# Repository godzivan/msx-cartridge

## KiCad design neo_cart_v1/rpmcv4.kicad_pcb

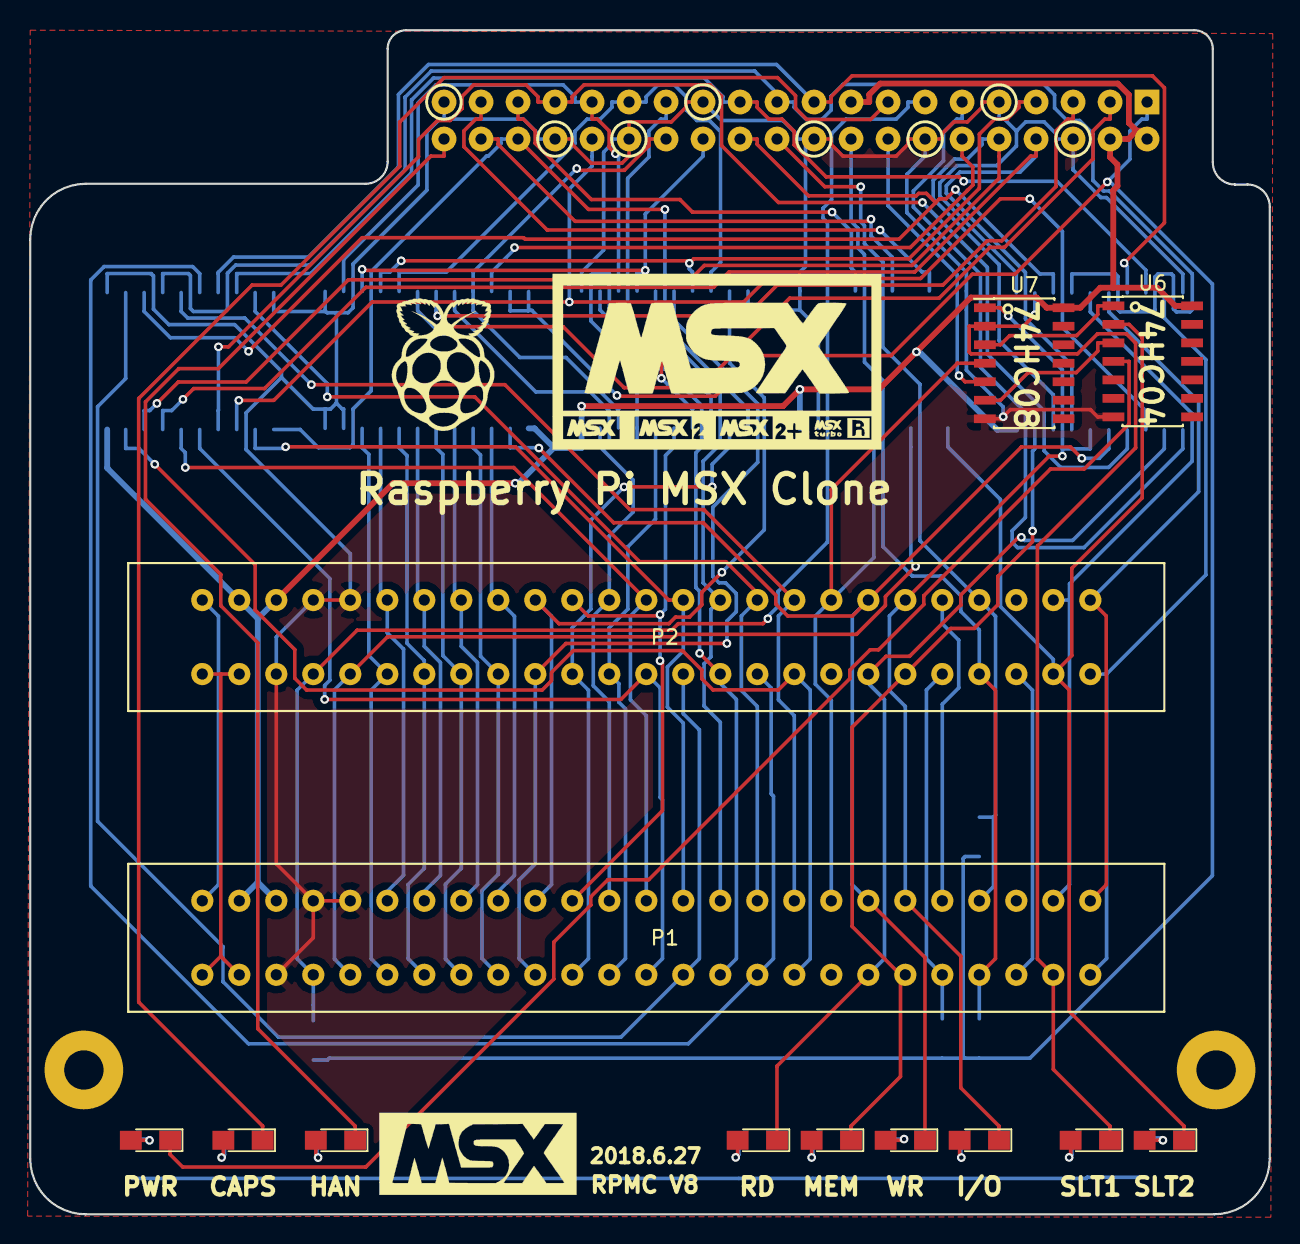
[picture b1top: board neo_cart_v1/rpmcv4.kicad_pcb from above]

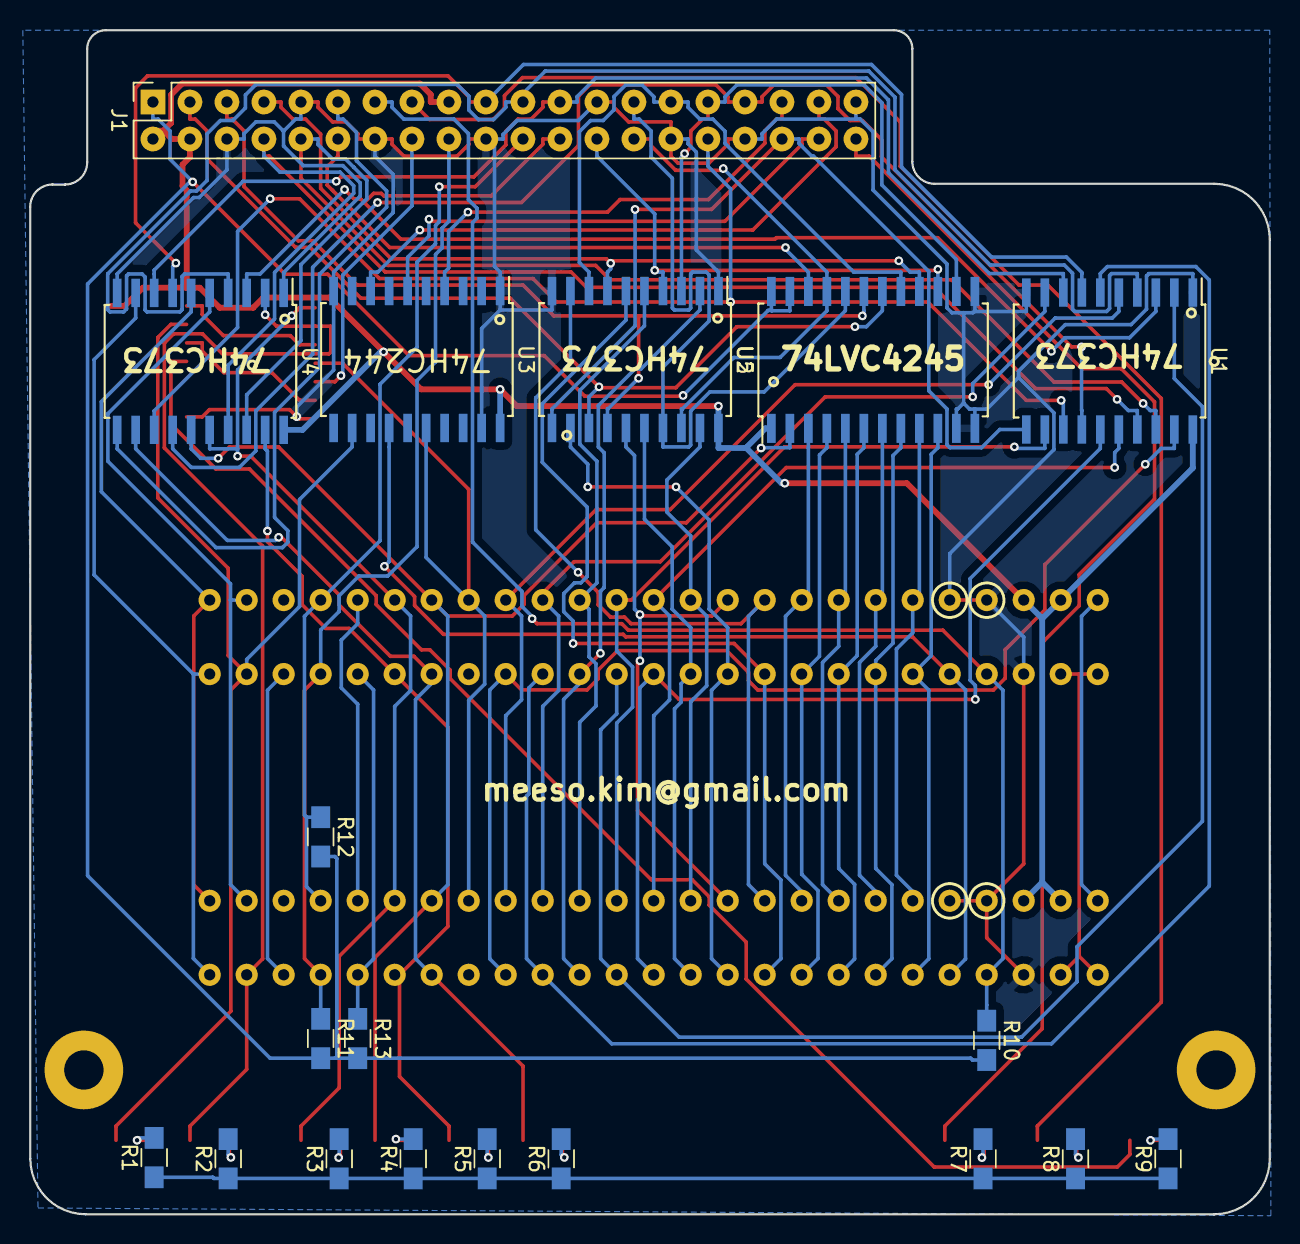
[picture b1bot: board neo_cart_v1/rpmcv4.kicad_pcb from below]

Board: 2 copper layers, 85.1 x 81.3 mm, 36 parts (19 on the bottom side), 84 nets.

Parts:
D1, D2, D3, D4, D5, D6, D7, D8, D9: Led_Small; LED_0805_HandSoldering
G1: LOGO; raspberry_pi_logo
G2: LOGO; msx_msx2_msx+logo
J1: RPi_GPIO; Socket_Strip_Straight_2x20_Pitch2.54mm
P1, P2: CONN_02X25; MSX_SLOT
R1, R2, R3, R4, R5, R6, R7, R8, R9, R10, R11, R12, R13: R; R_0805_HandSoldering
REF3, REF4: MountingHole_2.7mm_Pad
U1, U2, U4: 74LS373; SOIC-20W_7.5x12.8mm_Pitch1.27mm
U3: 74HC244; SOIC-20W_7.5x12.8mm_Pitch1.27mm
U5: LVC4245; SOIC-24W_7.5x15.4mm_Pitch1.27mm
U6: 74HC04; SOIC-14_3.9x8.7mm_Pitch1.27mm
U7: 74LS08; SOIC-14_3.9x8.7mm_Pitch1.27mm

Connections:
+3V3: J1.1, R10.2, R11.2, R12.2, R13.2, U5.23, U5.24
+5V: J1.2, J1.4, J1.17, P1.45, P1.47, P2.45, P2.47, U1.20, U2.20, U3.20, U4.20, U5.1, U6.14, U7.14
/+12V: P1.48, P1.50, P2.48, P2.50
/A0: P1.28, P2.28, U2.16
/A1: P1.27, P2.27, U2.19
/A2: P1.30, P2.30, U2.12
/A3: P1.29, P2.29, U2.15
/A4: P1.32, P2.32, U2.6
/A5: P1.31, P2.31, U2.9
/A6: P1.22, P2.22, U2.2
/A7: P1.21, P2.21, U2.5
/A8: P1.24, P2.24, U1.2
/A9: P1.17, P2.17, U1.5
/A10: P1.20, P2.20, U1.6
/A11: P1.19, P2.19, U1.9
/A12: P1.23, P2.23, U1.12
/A13: P1.26, P2.26, U1.15
/A14: P1.25, P2.25, U1.16
/A15: P1.18, P2.18, U1.19
/BUSDIR: P1.10, P2.10, R13.1
/CAPS: D8.1, J1.15
/CLK: P1.42, P2.42, U3.14
/CS1: P1.1, P2.1, U4.6
/CS2: P1.2, P2.2, U4.9
/CS12: P1.3, P2.3, U4.5
/D0: P1.34, P2.34, U5.4
/D1: P1.33, P2.33, U5.3
/D2: P1.36, P2.36, U5.6
/D3: P1.35, P2.35, U5.5
/D4: P1.38, P2.38, U5.8
/D5: P1.37, P2.37, U5.7
/D6: P1.40, P2.40, U5.10
/D7: P1.39, P2.39, U5.9
/HAN: D7.1, J1.40
/INT: J1.18, P1.8, P2.8, R11.1
/IORQ: D3.1, P1.11, P2.11, U4.16, U7.1
/M1: P1.9, P2.9
/MREQ: D5.1, P1.12, P2.12, U4.19
/PWR: D9.1, U6.4
/RA8: J1.24, U1.3, U4.3
/RA9: J1.21, U1.4, U4.4
/RA10: J1.19, U1.7, U4.7
/RA11: J1.23, U1.8, U4.8
/RA12: J1.32, U1.13, U4.13
/RA13: J1.33, U1.14, U4.14
/RA14: J1.8, U1.17, U4.17
/RA15: J1.10, U1.18, U4.18
/RC16: J1.36, U1.11, U2.11
/RC17: J1.11, U4.11
/RC18: J1.12, U5.22
/RC19: J1.35, U3.4
/RC20: J1.38, U3.6
/RC23: J1.16, U7.5
/RC25: J1.22, P1.7, P2.7, R12.1
/RC26: J1.37, U3.8
/RC27: J1.13, P1.44, P2.44, R10.1
/RD: D6.1, P1.14, P2.14, U4.12
/RD0: J1.27, U2.17, U5.20
/RD1: J1.28, U2.18, U5.21
/RD2: J1.3, U2.13, U5.18
/RD3: J1.5, U2.14, U5.19
/RD4: J1.7, U2.7, U5.16
/RD5: J1.29, U2.8, U5.17
/RD6: J1.31, U2.3, U5.14
/RD7: J1.26, U2.4, U5.15
/RESET: P1.15, P2.15, U3.16, U7.4
/RFSH: P1.6, P2.6
/SLTSL1: D2.1, P1.4, U4.2, U7.2
/SLTSL3: D1.1, P2.4, U3.12, U6.2
/SNDIN: P1.49, P2.49
/V3.3: R1.1, R2.1, R3.1, R4.1, R5.1, R6.1, R7.1, R8.1, R9.1
/WR: D4.1, P1.13, P2.13, U4.15, U5.2
/nPWR: U6.3, U7.6
/nSLTSL3: U6.1, U7.3
GND: J1.6, J1.9, J1.14, J1.20, J1.25, J1.30, J1.34, J1.39, P1.41, P1.43, P1.46, P2.41, P2.43, P2.46, U1.1, U1.10, U2.1, U2.10, U3.1, U3.10, U3.19, U4.1, U4.10, U5.11, U5.12, U5.13, U6.7, U7.7
unnamed: D1.2, R1.2
unnamed: D2.2, R2.2
unnamed: D3.2, R3.2
unnamed: D4.2, R4.2
unnamed: D5.2, R5.2
unnamed: D6.2, R6.2
unnamed: D7.2, R7.2
unnamed: D8.2, R8.2
unnamed: D9.2, R9.2

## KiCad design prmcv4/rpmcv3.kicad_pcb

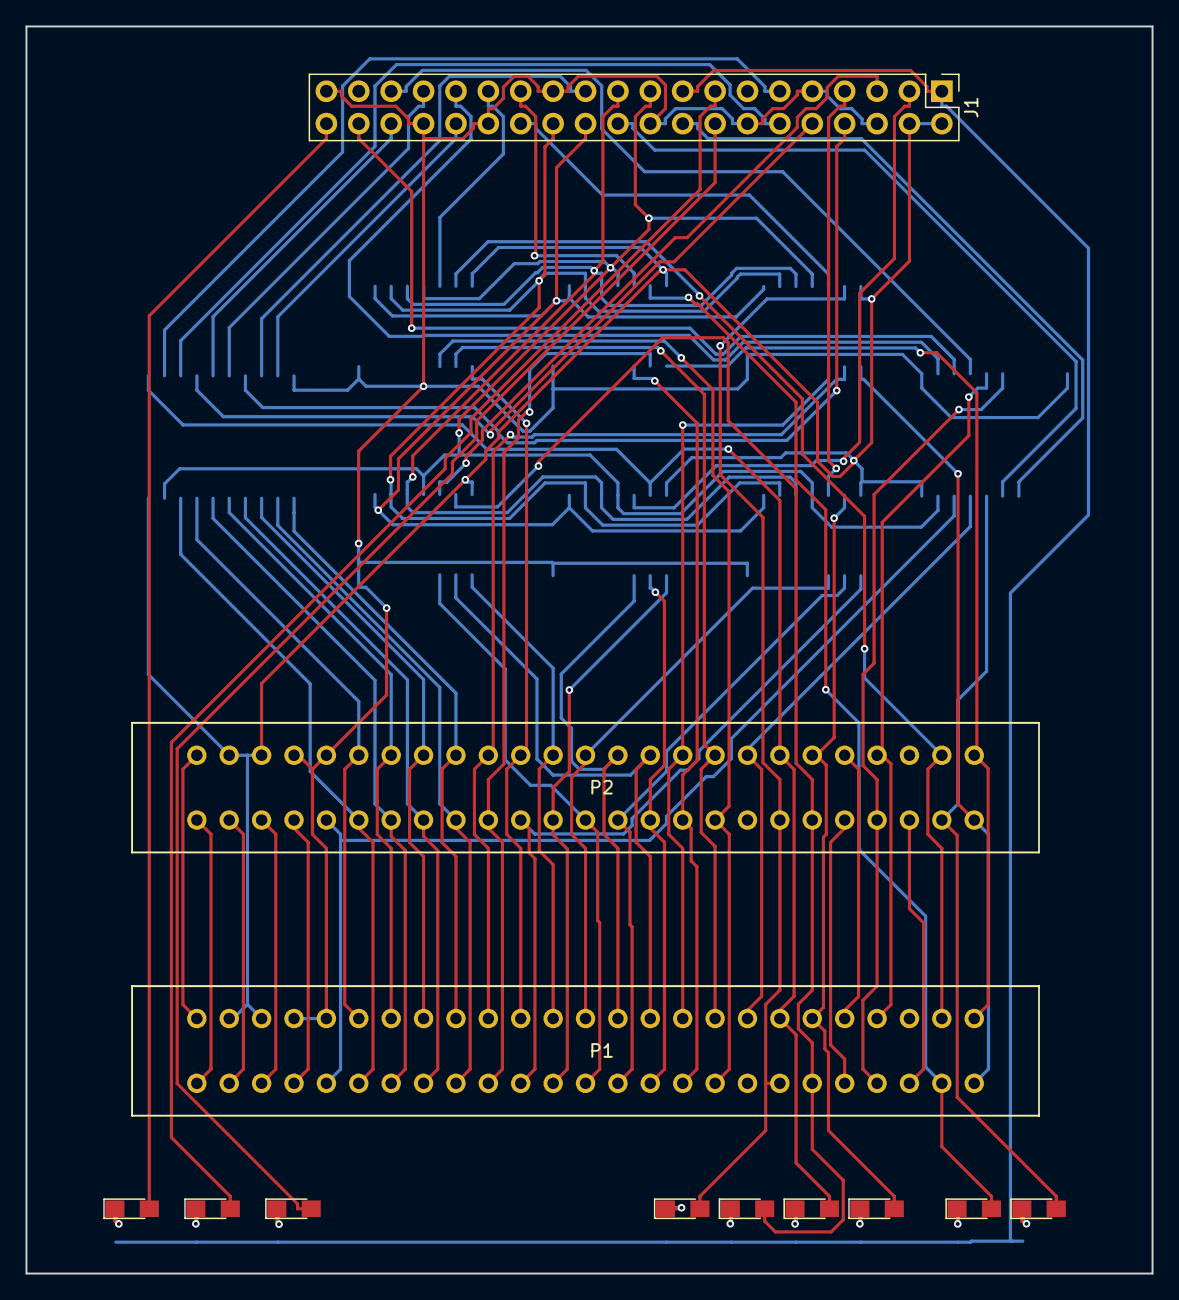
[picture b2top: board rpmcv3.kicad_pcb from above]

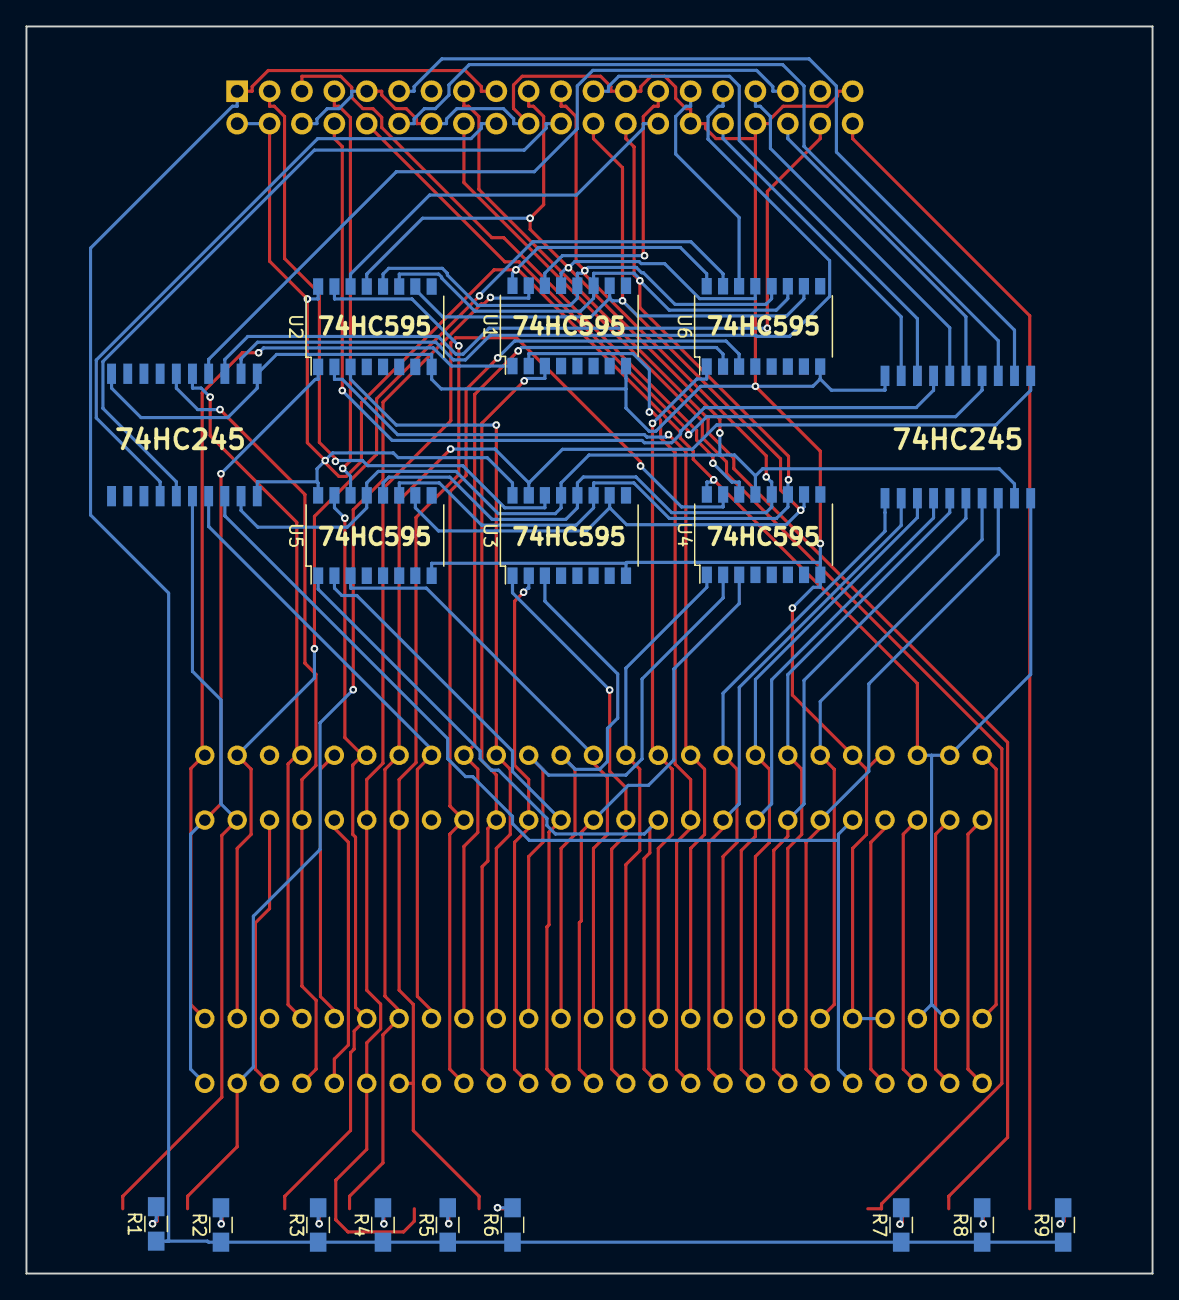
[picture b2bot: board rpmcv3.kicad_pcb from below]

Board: 2 copper layers, 88.3 x 97.8 mm, 29 parts (17 on the bottom side), 83 nets.

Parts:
D1, D2, D3, D4, D5, D6, D7, D8, D9: Led_Small; LED_0805_HandSoldering
J1: RPi_GPIO; Pin_Header_Straight_2x20_Pitch2.54mm
P1, P2: CONN_02X25; MSX_SLOT
R1, R2, R3, R4, R5, R6, R7, R8, R9: R; R_0805_HandSoldering
U1, U2, U3, U4, U5, U6: 74LS595; SOP-16_4.4x10.4mm_Pitch1.27mm
U7, U8: 74LS245; SOP20

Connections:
+3V3: J1.1, J1.17, R1.1, R2.1, R3.1, R4.1, R5.1, R6.1, R7.1, R8.1, R9.1
+5V: J1.2, J1.4, P1.45, P1.47, P2.45, P2.47, U1.16, U2.16, U3.16, U4.16, U5.16, U6.16, U7.20, U8.20
/+12V: P1.48, P2.48
/+V12: P1.50, P2.50
/A0: P1.28, P2.28, U3.1
/A1: P1.27, P2.27, U4.1
/A2: P1.30, P2.30, U5.1
/A3: P1.29, P2.29, U6.1
/A4: P1.32, P2.32, U1.2
/A5: P1.31, P2.31, U2.2
/A6: P1.22, P2.22, U3.2
/A7: P1.21, P2.21, U4.2
/A8: P1.24, P2.24, U5.2
/A9: P1.17, P2.17, U6.2
/A10: P1.20, P2.20, U1.3
/A11: P1.19, P2.19, U2.3
/A12: P1.23, P2.23, U3.3
/A13: P1.26, P2.26, U4.3
/A14: P1.25, P2.25, U5.3
/A15: P1.18, P2.18, U6.3
/BUSDIR: P1.10, P2.10
/CAPS: D8.2, J1.15
/CLK: P1.42, P2.42, U7.18
/CS1: P1.1, P2.1, U1.1
/CS2: P1.2, P2.2, U2.1
/CS12: P1.3, P2.3, U6.15
/D0: P1.34, P2.34, U8.12
/D1: P1.33, P2.33, U8.11
/D2: P1.36, P2.36, U8.14
/D3: P1.35, P2.35, U8.13
/D4: P1.38, P2.38, U8.16
/D5: P1.37, P2.37, U8.15
/D6: P1.40, P2.40, U8.18
/D7: P1.39, P2.39, U8.17
/HAN: D7.2, J1.16
/INT: P1.8, P2.8, U7.6
/IORQ: D3.2, P1.11, P2.11, U5.15
/LATCH: J1.21, U1.12, U2.12, U3.12, U4.12, U5.12, U6.12
/M1: P1.9, P2.9
/MOSI0: J1.27, U1.14
/MOSI1: J1.28, U2.14
/MOSI2: J1.3, U3.14
/MOSI3: J1.5, U4.14
/MOSI4: J1.7, U5.14
/MOSI5: J1.29, U6.14
/MREQ: D5.2, P1.12, P2.12, U4.15
/OE: J1.19, U1.13, U2.13, U3.13, U4.13, U5.13, U6.13, U7.19, U8.19
/PWR: D9.2, J1.40
/RCLK: J1.31, U7.2
/RD: D6.2, P1.14, P2.14, U2.15
/RD0: J1.23, U8.8
/RD1: J1.32, U8.9
/RD2: J1.33, U8.6
/RD3: J1.8, U8.7
/RD4: J1.10, U8.4
/RD5: J1.36, U8.5
/RD6: J1.11, U8.2
/RD7: J1.12, U8.3
/RESET: P1.15, P2.15, U7.17
/RFSH: P1.6, P2.6
/RINT: J1.18, U7.14
/RRESET: J1.38, U7.3
/RSLTSL3: J1.35, U7.4
/RWAIT: J1.22, U7.15
/SLTSL1: D2.2, P1.4, U1.15
/SLTSL3: D1.2, P2.4, U7.16
/SNDIN: P1.49, P2.49
/SRCLK: J1.26, U1.11, U2.11, U3.11, U4.11, U5.11, U6.11
/SRCLR: J1.24, U1.10, U2.10, U3.10, U4.10, U5.10, U6.10
/SW1: P1.44, P2.44
/SW2: P1.46, P2.46
/WAIT: P1.7, P2.7, U7.5
/WR: D4.2, P1.13, P2.13, U3.15, U8.1
GND: J1.6, J1.9, J1.14, J1.20, J1.25, J1.30, J1.34, J1.39, P1.41, P1.43, P2.41, P2.43, U1.8, U2.8, U3.8, U4.8, U5.8, U6.8, U7.1, U7.10, U8.10
unnamed: D1.1, R1.2
unnamed: D2.1, R2.2
unnamed: D3.1, R3.2
unnamed: D4.1, R4.2
unnamed: D5.1, R5.2
unnamed: D6.1, R6.2
unnamed: D7.1, R7.2
unnamed: D8.1, R8.2
unnamed: D9.1, R9.2

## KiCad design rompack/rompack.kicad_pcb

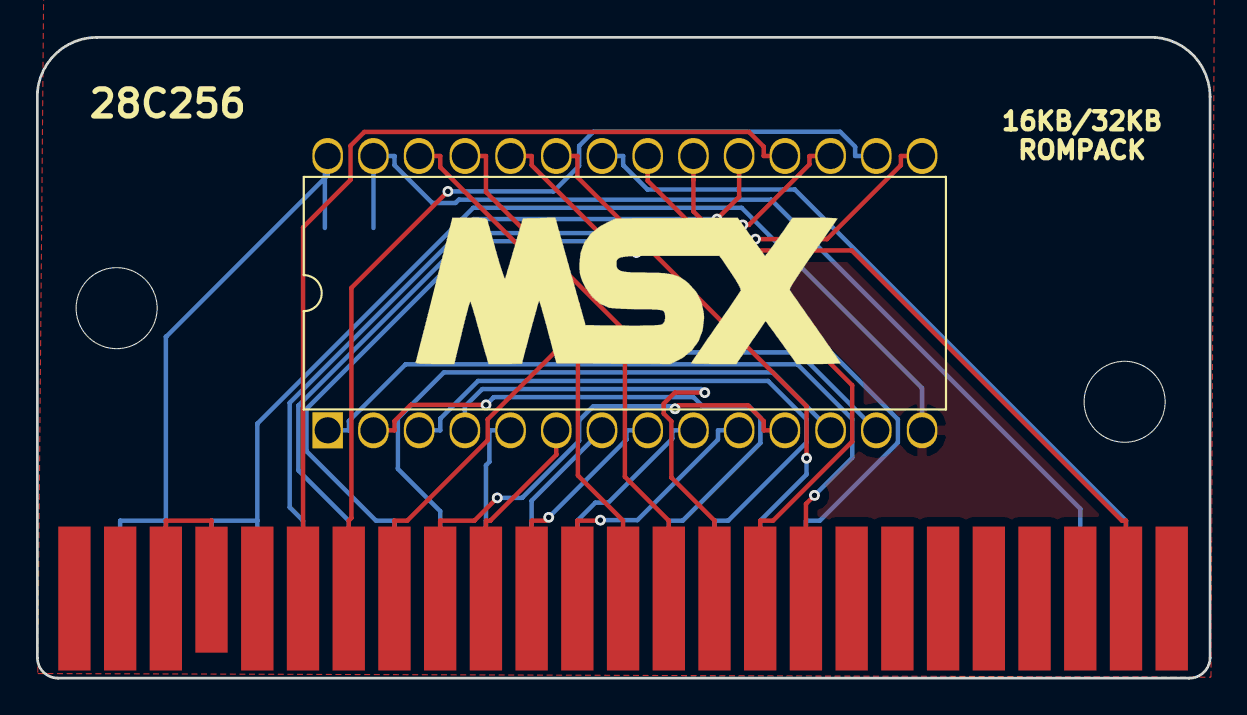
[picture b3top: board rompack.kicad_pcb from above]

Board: 2 copper layers, 65.2 x 35.6 mm, 4 parts (1 on the bottom side), 29 nets.

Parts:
G1: LOGO; msx-logo
P1: CONN_MSXSLOT; card_edge_connector
R1: R; R_0805_HandSoldering
U1: 28C256; DIP-28_W15.24mm

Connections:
/A0: P1.28, U1.10
/A1: P1.27, U1.9
/A2: P1.30, U1.8
/A3: P1.29, U1.7
/A4: P1.32, U1.6
/A5: P1.31, U1.5
/A6: P1.22, U1.4
/A7: P1.21, U1.3
/A8: P1.24, U1.25
/A9: P1.17, U1.24
/A10: P1.20, U1.21
/A11: P1.19, U1.23
/A12: P1.23, U1.2
/A13: P1.26, U1.26
/A14: P1.18, U1.1
/CS12: P1.3, U1.22
/D0: P1.34, U1.11
/D1: P1.33, U1.12
/D2: P1.36, U1.13
/D3: P1.35, U1.15
/D4: P1.38, U1.16
/D5: P1.37, U1.17
/D6: P1.40, U1.18
/D7: P1.39, U1.19
/SLTSL: P1.4, U1.20
/WR0: P1.5, R1.1, U1.27
GND: P1.41, P1.43, U1.14
unnamed: P1.44, P1.46
VCC: P1.45, P1.47, R1.2, U1.28

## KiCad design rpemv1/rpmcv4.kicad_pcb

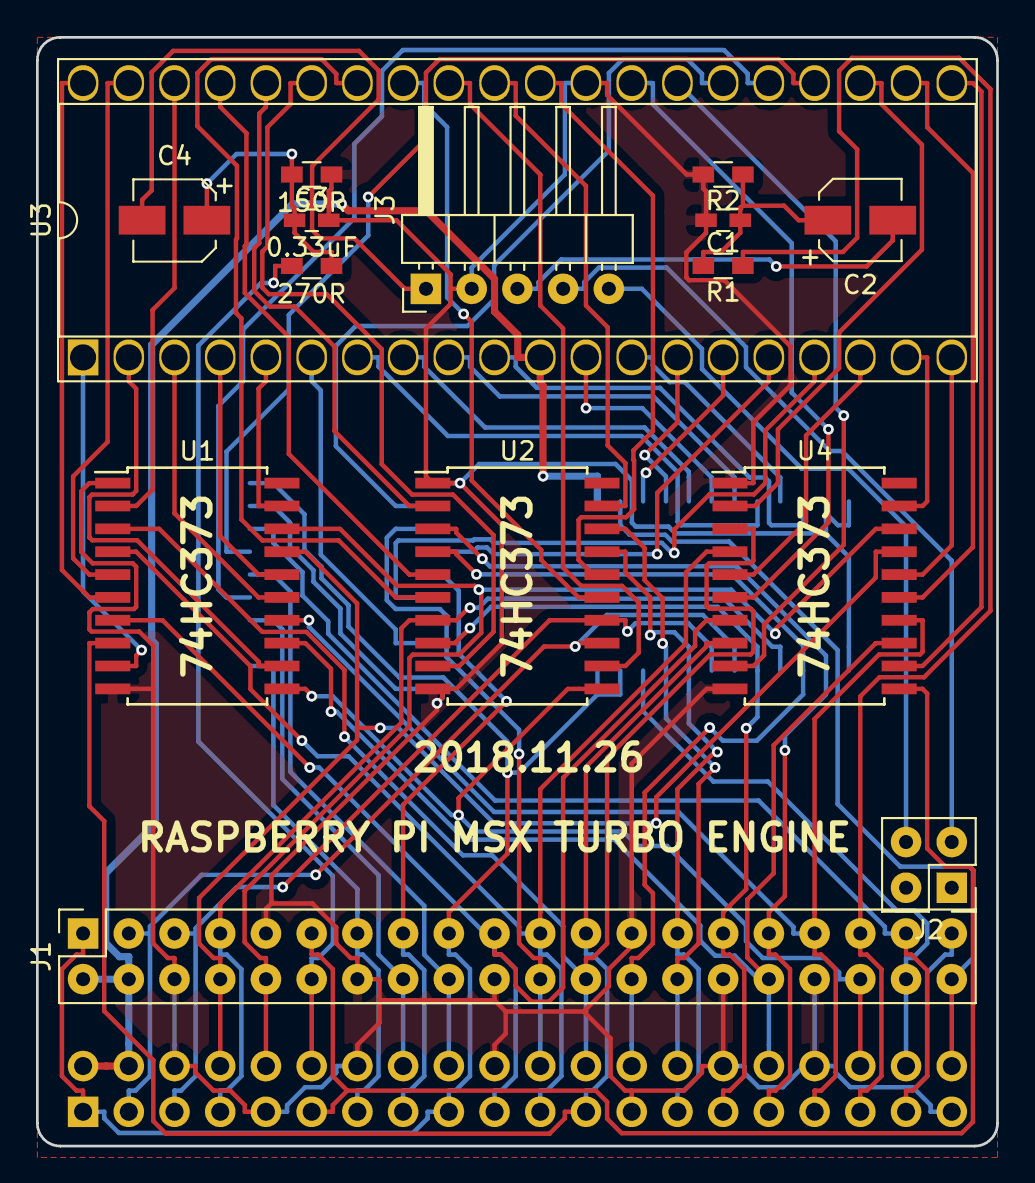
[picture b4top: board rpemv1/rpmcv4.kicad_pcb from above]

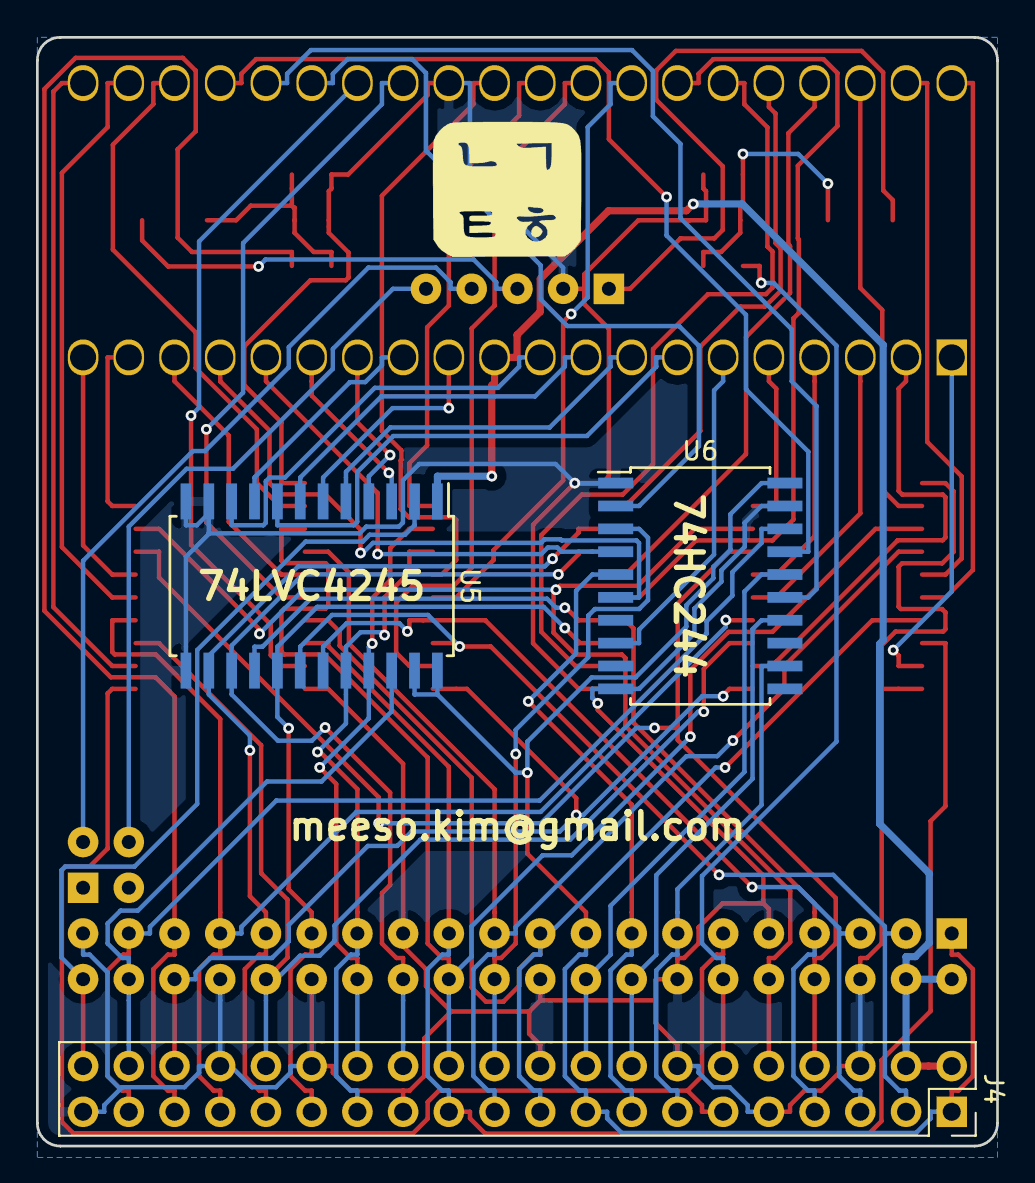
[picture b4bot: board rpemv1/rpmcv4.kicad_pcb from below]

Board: 2 copper layers, 53.3 x 61.6 mm, 18 parts (3 on the bottom side), 75 nets.

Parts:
C1, C3: 0.33uF; C_0603_HandSoldering
C2, C4: 10uF; CP_Elec_4x4.5
J1, J4: RPi_GPIO; Socket_Strip_Straight_2x20_Pitch2.54mm
J2: Conn_02x02_Odd_Even; Pin_Header_Straight_2x02_Pitch2.54mm
J3: Conn_01x05_Male; Pin_Header_Angled_1x05_Pitch2.54mm
R1, R3: 270R; R_0603_HandSoldering
R2, R4: 150R; R_0603_HandSoldering
U1, U2, U4: 74LS373; SOIC-20W_7.5x12.8mm_Pitch1.27mm
U3: Z80CPU; DIP-40_W15.24mm_Socket
U5: LVC4245; SOIC-24W_7.5x15.4mm_Pitch1.27mm
U6: 74HC244; SOIC-20W_7.5x12.8mm_Pitch1.27mm

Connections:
+3V3: J1.1, J1.17, J4.1, J4.17, U5.23, U5.24, U6.20
+5V: J1.2, J1.4, J4.2, J4.4, U3.11, U5.1
/A0: U2.16, U3.30
/A1: U2.19, U3.31
/A2: U2.12, U3.32
/A3: U2.15, U3.33
/A4: U2.6, U3.34
/A5: U2.9, U3.35
/A6: U2.2, U3.36
/A7: U2.5, U3.37
/A8: U1.2, U3.38
/A9: U1.5, U3.39
/A10: U1.6, U3.40
/A11: U1.9, U3.1
/A12: U1.12, U3.2
/A13: U1.15, U3.3
/A14: U1.16, U3.4
/A15: U1.19, U3.5
/BUSACK: U3.23, U4.2
/BUSRQ: U3.25, U6.15
/CLK: U3.6, U6.8
/D0: U3.14, U5.4
/D1: U3.15, U5.3
/D2: U3.12, U5.6
/D3: U3.8, U5.5
/D4: U3.7, U5.8
/D5: U3.9, U5.7
/D6: U3.10, U5.10
/D7: U3.13, U5.9
/HALT: U3.18, U4.5
/INT: U3.16, U6.4
/IORQ: U3.20, U4.16
/M1: U3.27, U4.9
/MREQ: U3.19, U4.19
/NMI: U3.17, U6.6
/RA8: J1.24, J4.24, U1.3, U4.3
/RA9: J1.21, J4.21, U1.4, U4.4
/RA10: J1.19, J4.19, U1.7, U4.7
/RA11: J1.23, J4.23, U1.8, U4.8
/RA12: J1.32, J4.32, U1.13, U4.13
/RA13: J1.33, J4.33, U1.14, U4.14
/RA14: J1.8, J4.8, U1.17, U4.17
/RA15: J1.10, J4.10, U1.18, U4.18
/RC16: J1.36, J4.36, U1.11, U2.11
/RC17: J1.11, J4.11, U4.11
/RC18: J1.12, J4.12, R3.1
/RC19: J1.35, J4.35, R1.1
/RC20: J1.38, J4.38, U5.22
/RC21: J1.40, J4.40, U5.2
/RC22: J1.15, J4.15, U6.5
/RC23: J1.16, J4.16, U6.14
/RC24: J1.18, J4.18, U6.16
/RC25: J1.22, J4.22, U6.3
/RC26: J1.37, J4.37, U6.18
/RC27: J1.13, J4.13, U6.12
/RD: U3.21, U4.12
/RD0: J1.27, J4.27, U2.17, U5.20
/RD1: J1.28, J4.28, U2.18, U5.21
/RD2: J1.3, J4.3, U2.13, U5.18
/RD3: J1.5, J4.5, U2.14, U5.19
/RD4: J1.7, J4.7, U2.7, U5.16
/RD5: J1.29, J4.29, U2.8, U5.17
/RD6: J1.31, J4.31, U2.3, U5.14
/RD7: J1.26, J4.26, U2.4, U5.15
/RESET: U3.26, U6.2
/RFSH: U3.28, U4.6
/WAIT: U3.24, U6.17
/WR: U3.22, U4.15
GND: C1.2, C3.2, J1.6, J1.9, J1.14, J1.20, J1.25, J1.30, J1.34, J1.39, J3.2, J4.6, J4.9, J4.14, J4.20, J4.25, J4.30, J4.34, J4.39, R2.2, R4.2, U1.1, U1.10, U2.1, U2.10, U3.29, U4.1, U4.10, U5.11, U5.12, U5.13, U6.1, U6.10, U6.19
unnamed: C1.1, C2.1, R1.2, R2.1
unnamed: C2.2, J3.3
unnamed: C3.1, C4.1, R3.2, R4.1
unnamed: C4.2, J3.1
unnamed: J2.3, J3.4
unnamed: J2.4, J3.5

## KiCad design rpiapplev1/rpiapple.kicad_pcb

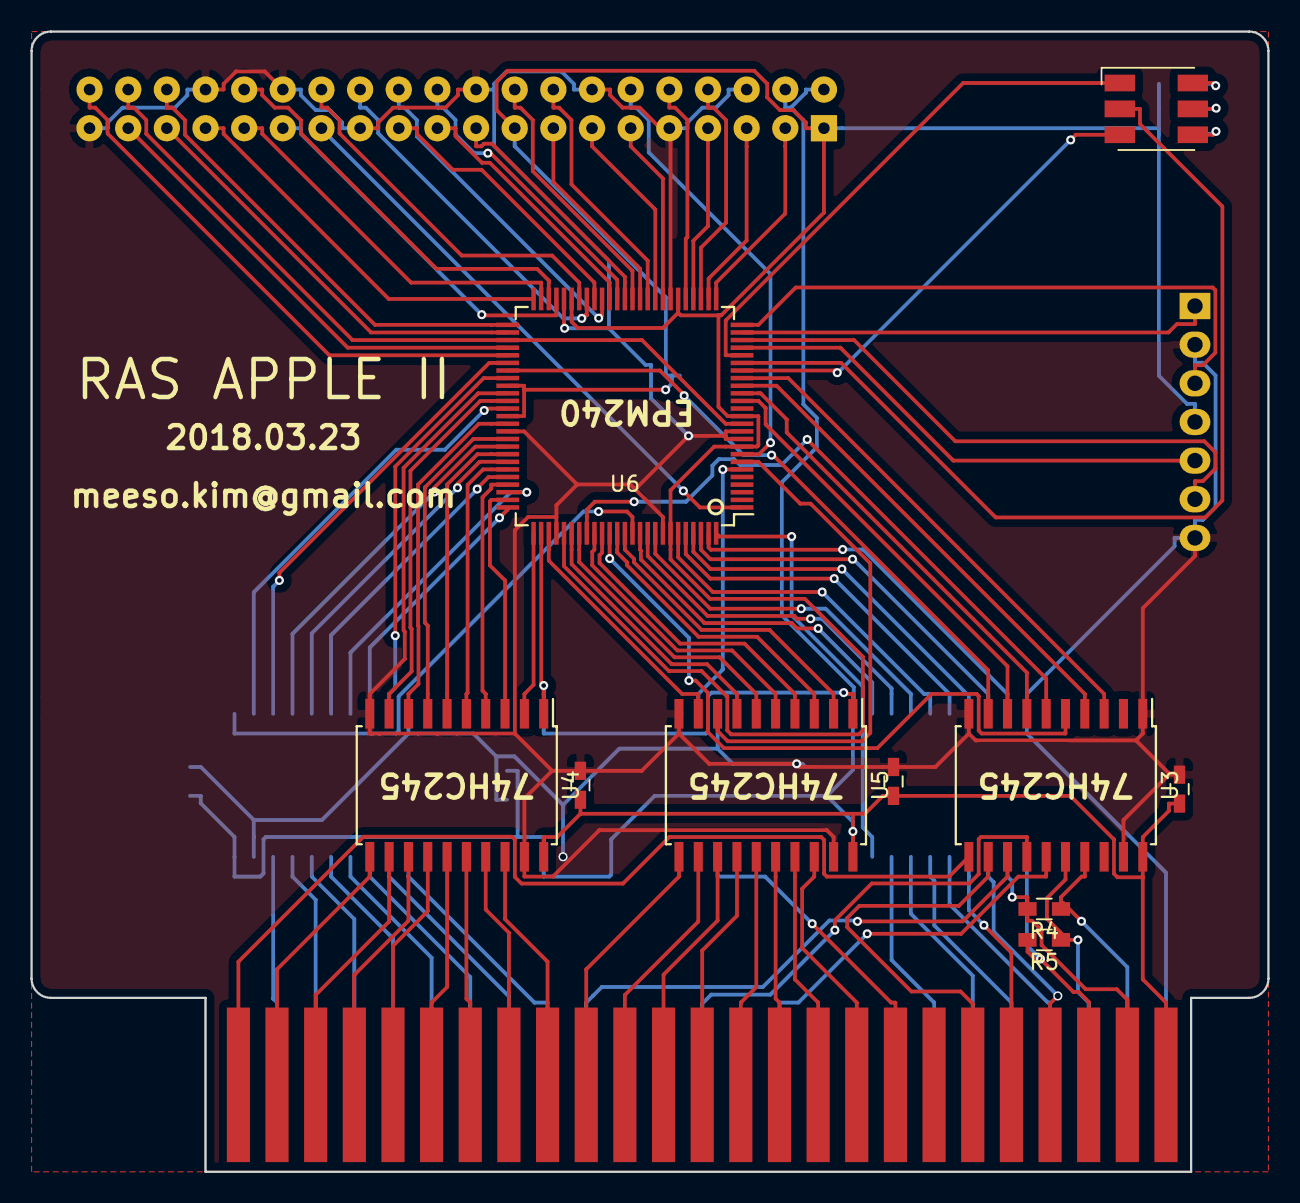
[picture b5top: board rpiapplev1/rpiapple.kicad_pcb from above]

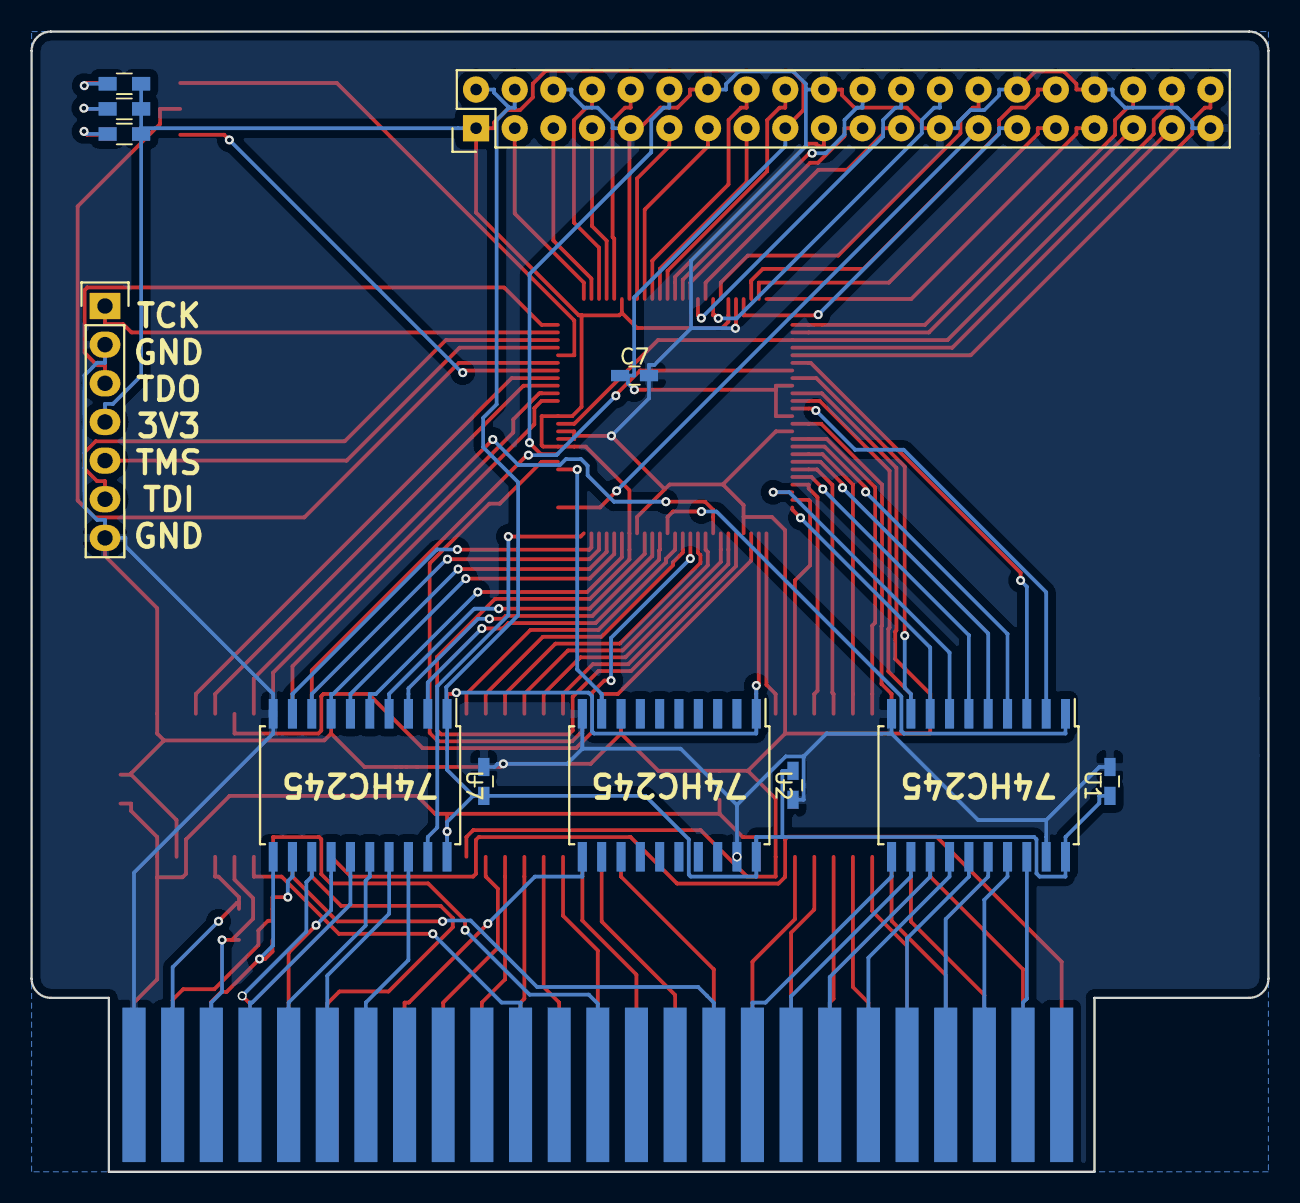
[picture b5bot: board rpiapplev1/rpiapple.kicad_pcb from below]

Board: 2 copper layers, 81.3 x 74.9 mm, 23 parts (12 on the bottom side), 124 nets.

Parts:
C1, C2, C3, C4, C5, C6, C7: C; C_0603_HandSoldering
D1: LED_RGB; LED_RGB_5050-6
J1: Raspberry_Pi_2_3; Pin_Header_Straight_2x20
J2: Conn_01x07; Pin_Header_Straight_1x07
P1: A2Bus; Male_Card-Edge_50_pin__100_mil
R1, R2, R3, R4, R5: R; R_0603_HandSoldering
U1, U2, U3, U4, U5, U7: 74HC245; SOIC-20W_7.5x12.8mm_Pitch1.27mm
U6: EMP240; TQFP-100_14x14mm_Pitch0.5mm

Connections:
/3V3: C7.1, J1.1, J1.17, J2.4, R1.1, R2.1, R3.1, U6.9, U6.13, U6.31, U6.45, U6.59, U6.63, U6.80, U6.94
/7M: P1.36, U3.15
/A0: P1.2, U4.11
/A1: P1.3, U4.12
/A2: P1.4, U4.13
/A3: P1.5, U4.14
/A4: P1.6, U4.15
/A5: P1.7, U4.16
/A6: P1.8, U4.17
/A7: P1.9, U4.18
/A8: P1.10, U5.11
/A9: P1.11, U5.12
/A10: P1.12, U5.13
/A11: P1.13, U5.14
/A12: P1.14, U5.15
/A13: P1.15, U5.16
/A14: P1.16, U5.17
/A15: P1.17, U5.18
/D0: P1.49, U1.18
/D1: P1.48, U1.17
/D2: P1.47, U1.16
/D3: P1.46, U1.15
/D4: P1.45, U1.14
/D5: P1.44, U1.13
/D6: P1.43, U1.12
/D7: P1.42, U1.11
/DEVSEL: P1.41, U3.13
/DMA: P1.22, U7.13
/DMAI: P1.27, R4.1, U3.17
/DMAO: P1.24, R4.2, U7.12
/INH: P1.32, U7.18
/INT0: P1.23, R5.2, U7.11
/INTI: P1.28, R5.1, U3.16
/IOSEL: P1.1, U3.11
/IOSTRB: P1.20, U3.12
/IRQ: P1.30, U7.16
/LED1: D1.3, U6.19
/LED2: D1.2, U6.20
/LED3: D1.1, U6.21
/NMI: P1.29, U7.15
/PH1: P1.38, U3.14
/RA0: J1.24, U6.41
/RA1: J1.21, U6.40
/RA2: J1.19, U6.38
/RA3: J1.23, U6.42
/RA4: J1.32, U6.48
/RA5: J1.33, U6.50
/RA6: J1.8, U6.28
/RA7: J1.10, U6.30
/RC0: J1.36, U6.51
/RC1: J1.11, U6.33
/RC2: J1.12, U6.8
/RC3: J1.35, U6.52
/RC4: J1.38, U6.12, U6.53
/RC5: J1.40, U6.55
/RC6: J1.15, U6.36
/RC7: J1.16, U6.35
/RC8: J1.18, U6.37
/RC9: J1.22, U6.39
/RC10: J1.37, U6.54
/RC11: J1.13, U6.34
/RD0: J1.27, U6.1
/RD1: J1.28, U6.44
/RD2: J1.3, U6.26
/RD3: J1.5, U6.27
/RD4: J1.7, U6.29
/RD5: J1.29, U6.47
/RD6: J1.31, U6.49
/RD7: J1.26, U6.43
/RDY: P1.21, U7.14
/RES: P1.31, U7.17
/RW: P1.18, U2.11
/T7M: U3.5, U6.86
/TA0: U4.9, U6.61
/TA1: U4.8, U6.64
/TA2: U4.7, U6.66
/TA3: U4.6, U6.68
/TA4: U4.5, U6.70
/TA5: U4.4, U6.72
/TA6: U4.3, U6.74
/TA7: U4.2, U6.76
/TA8: U5.9, U6.78
/TA9: U5.8, U6.7
/TA10: U5.7, U6.81
/TA11: U5.6, U6.82
/TA12: U5.5, U6.84
/TA13: U5.4, U6.85
/TA14: U5.3, U6.87
/TA15: U5.2, U6.88
/TCK: J2.1, U6.24
/TD0: U1.2, U6.62
/TD1: U1.3, U6.56
/TD2: U1.4, U6.67
/TD3: U1.5, U6.69
/TD4: U1.6, U6.71
/TD5: U1.7, U6.73
/TD6: U1.8, U6.75
/TD7: U1.9, U6.58
/TDEVSEL: U3.7, U6.16
/TDI: J2.6, U6.23
/TDIR: U2.1, U4.1, U5.1, U6.77
/TDIR2: U6.100, U7.19
/TDMA: U6.97, U7.7
/TDMAI: U3.3, U6.18
/TDMAO: U6.98, U7.8
/TDO: J2.3, U6.25
/TINH: U6.90, U7.2
/TINTI: U3.4, U6.17
/TINTO: U6.99, U7.9
/TIOSEL: U3.9, U6.57
/TIOSTRB: U3.8, U6.15
/TIRQ: U6.92, U7.4
/TMS: J2.5, U6.22
/TNMI: U6.95, U7.5
/TPH1: U3.6, U6.83
/TRDY: U6.96, U7.6
/TRES: U6.91, U7.3
/TRW: U2.9, U6.6
/TWR: U1.1, U6.89
GND: C1.2, C2.2, C3.2, C4.2, C5.2, C6.2, C7.2, J1.6, J1.9, J1.14, J1.20, J1.25, J1.30, J1.34, J1.39, J2.2, J2.7, P1.26, U1.10, U1.19, U2.10, U2.19, U3.1, U3.10, U3.19, U4.10, U4.19, U5.10, U5.19, U6.10, U6.11, U6.32, U6.46, U6.60, U6.65, U6.79, U6.93, U7.10
unnamed: D1.4, R3.2
unnamed: D1.5, R2.2
unnamed: D1.6, R1.2
VCC: C1.1, C2.1, C3.1, C4.1, C5.1, C6.1, J1.2, J1.4, P1.25, U1.20, U2.20, U3.20, U4.20, U5.20, U7.1, U7.20
